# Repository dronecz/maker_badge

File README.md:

# Info
This project was moved [here](https://github.com/makerfaireczech/maker_badge)

## Where I can buy it? 

[Makermarket](https://www.makermarket.cz/maker-badge/)

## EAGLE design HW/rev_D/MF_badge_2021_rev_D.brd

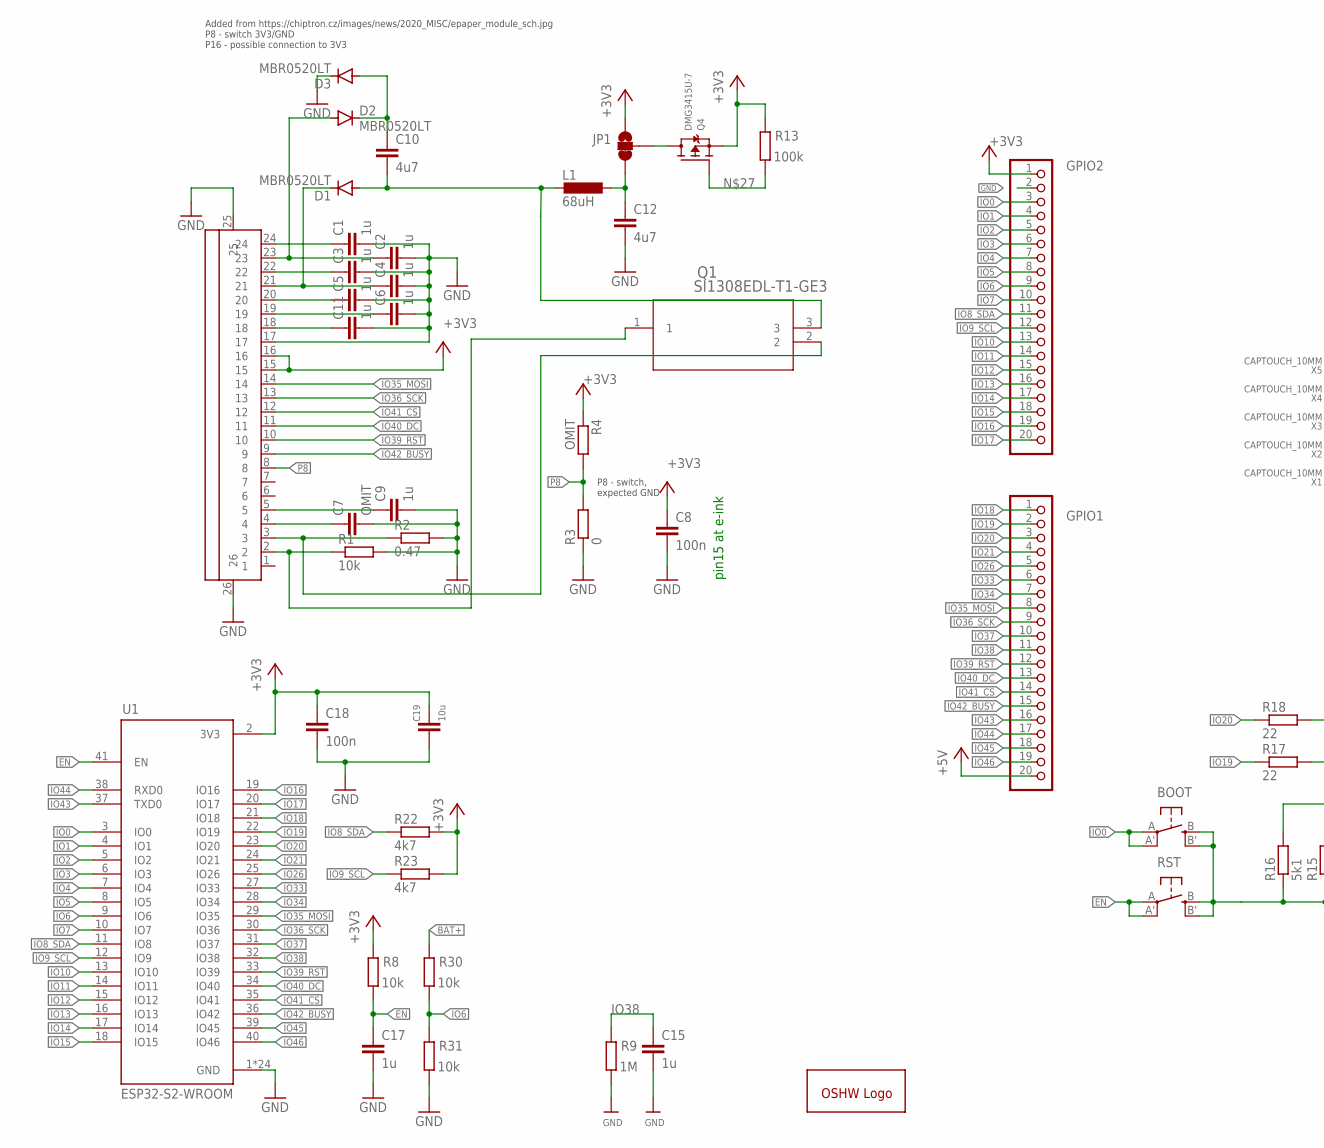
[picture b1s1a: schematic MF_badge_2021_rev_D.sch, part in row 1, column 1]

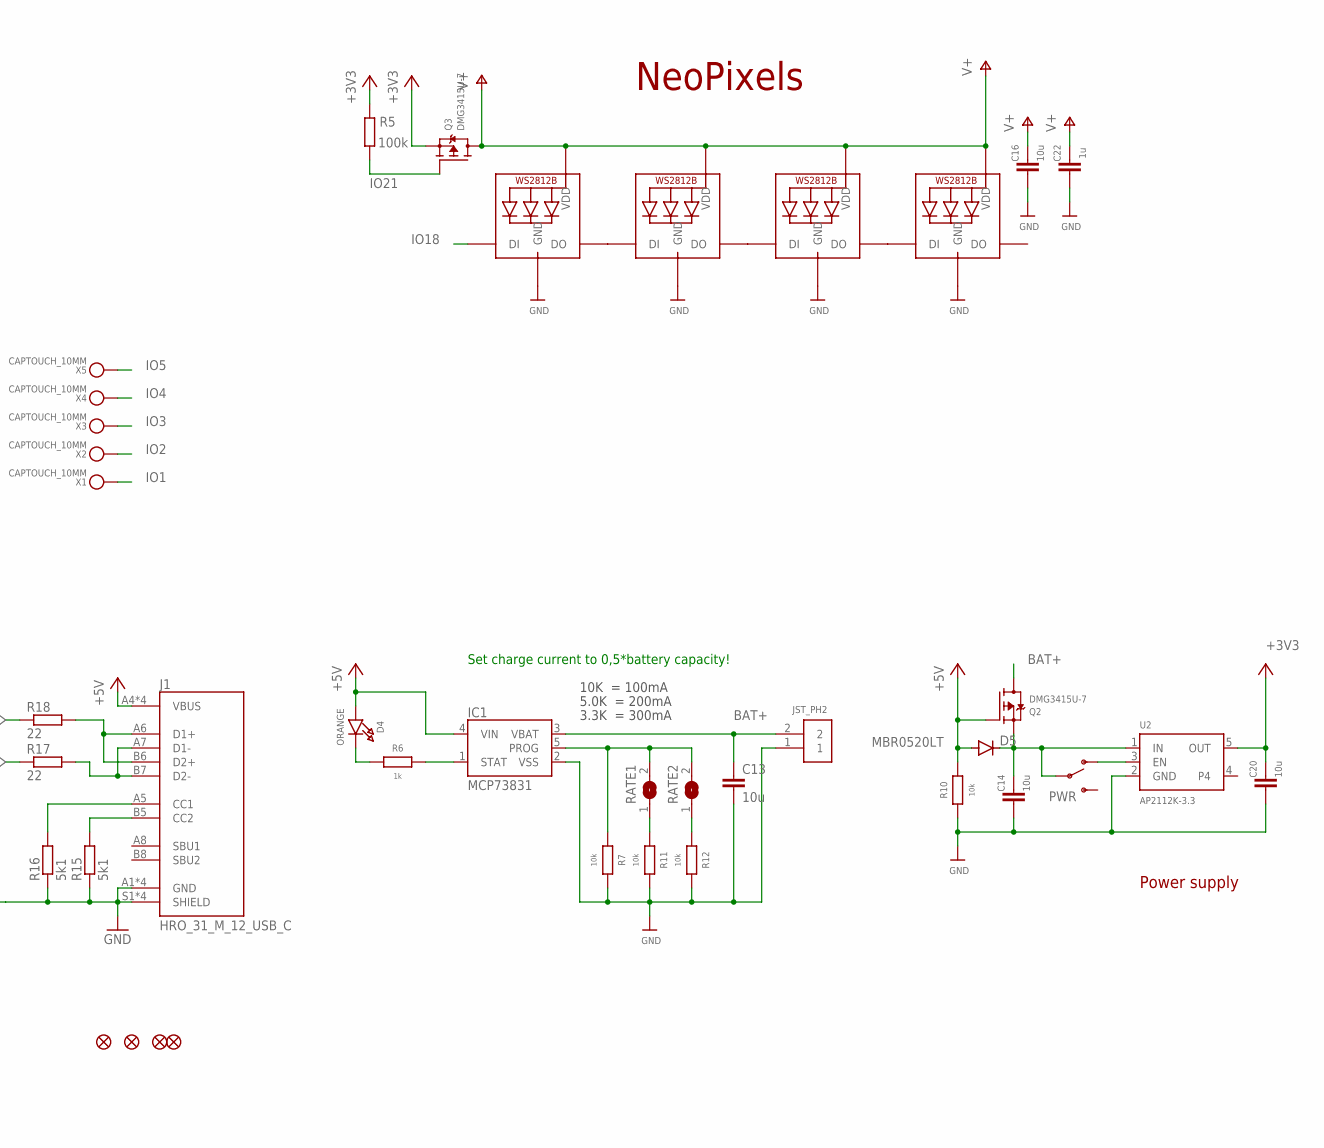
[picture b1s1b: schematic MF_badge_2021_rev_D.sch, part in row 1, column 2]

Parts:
BOOT: BUTTON_KMR2_4.6X2.8
C1, C2, C3, C4, C5, C6, C9, C11, C15, C17, C22: 1u; C0805
C7: OMIT; C0805
C8, C18: 100n; C0805
C10, C12: 4u7; C0805
C13, C14, C16, C19, C20: 10u; C0805
D1, D2, D3, D5: MBR0520LT; SOD123
D4: ORANGE; CHIPLED_0805_NOOUTLINE
FID1, FID2, FID3, FID4: FIDUCIAL_1MM
GOLD_ORB_SM1: OSHWLOGO_; OSHW_5MM_LOGO
GPIO1, GPIO2: PINHD-1X20; 1X20
IC1: MCP73831; SOT95P290X120-5
J1: HRO_31_M_12_USB_C
JP1: JUMPER-SMT_3_1-NC_TRACE_NO-SILK; SMT-JUMPER_3_1-NC_TRACE_NO-SILK
L1: 68uH; L4532P
LED2, LED3, LED4, LED5: WS2812B5050; WS2812B
PWR: SWITCH-SPDT-SMD-RIGHT-ANGLE; SWITCH_SPST_SMD_A
Q1: SI1308EDL-T1-GE3; MOSFET_8EDL-T1-GE3_VIS
Q2, Q3, Q4: DMG3415U-7; SOT23-R
R1, R7, R8, R10, R11, R12, R30, R31: 10k; R0805
R2: 0.47; R0805
R3: 0; R0805
R4: OMIT; R0805
R5, R13: 100k; R0805
R6: 1k; R0805
R9: 1M; R0805
R15, R16: 5k1; R0805
R17, R18: 22; R0805
R22, R23: 4k7; R0805
RATE1, RATE2: SOLDERJUMPER; SOLDERJUMPER_ARROW_NOPASTE
RST: BUTTON_KMR2_4.6X2.8
U1: ESP32-S2-WROOM; XCVR_ESP32-S2-WROOM
U2: AP2112K-3.3; SOT23-5
U$1: 2.13_EINK
U$8: JST_PH2; JSTPH2
X1, X2, X3, X4, X5: CAPTOUCH_10MM; CAPTOUCH_6X9MM

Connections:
+3V3: C8.1, C18.1, C19.1, C20.1, GPIO2.1, JP1.1, Q3.2 (S), Q4.2 (S), R4.1, R5.2, R8.2, R13.2, R22.2, R23.2, U1.2 (3V3), U2.5 (OUT), U$1.15, U$1.16
+5V: D4.A, D5.A, GPIO1.20, IC1.4 (VIN), J1.A4 (VBUS), J1.A9 (VBUS), J1.B4 (VBUS), J1.B9 (VBUS), Q2.1 (G), R10.2
BAT+: C13.1, IC1.3 (VBAT), Q2.3 (D), R30.2, U$8.2
D+_CON: J1.A6 (D1+), J1.B6 (D2+), R18.2
D-_CON: J1.A7 (D1-), J1.B7 (D2-), R17.2
EN: C17.1, R8.1, RST.A, RST.A' (P1), U1.41 (EN)
GND: BOOT.B (S), BOOT.B' (S1), C1.2, C2.2, C3.2, C4.2, C5.2, C6.2, C7.2, C8.2, C9.2, C11.2, C12.2, C13.2, C14.2, C15.2, C16.2, C17.2, C18.2, C19.2, C20.2, C22.2, D3.C, GPIO2.2, IC1.2 (VSS), J1.A1 (GND), J1.A12 (GND), J1.B1 (GND), J1.B12 (GND), J1.S1 (SHIELD), J1.S2 (SHIELD), J1.S3 (SHIELD), J1.S4 (SHIELD), LED2.3-GND (GND), LED3.3-GND (GND), LED4.3-GND (GND), LED5.3-GND (GND), R1.2, R2.2, R3.1, R7.2, R9.1, R10.1, R11.2, R12.2, R15.1, R16.1, R31.1, RST.B (S), RST.B' (S1), U1.1 (GND), U1.26 (GND), U1.42 (GND), U1.43.1 (GND), U1.43.2 (GND), U1.43.3 (GND), U1.43.4 (GND), U1.43.5 (GND), U1.43.6 (GND), U1.43.7 (GND), U1.43.8 (GND), U1.43.9 (GND), U1.43.10 (GND), U1.43.11 (GND), U1.43.12 (GND), U1.43.13 (GND), U1.43.14 (GND), U1.43.15 (GND), U1.43.16 (GND), U1.43.17 (GND), U1.43.18 (GND), U1.43.19 (GND), U1.43.20 (GND), U1.43.21 (GND), U2.2 (GND), U$1.17, U$1.25, U$1.26, U$8.1
IO0: BOOT.A, BOOT.A' (P1), GPIO2.3, U1.3 (IO0)
IO1: GPIO2.4, U1.4 (IO1), X1.P$1
IO2: GPIO2.5, U1.5 (IO2), X2.P$1
IO3: GPIO2.6, U1.6 (IO3), X3.P$1
IO4: GPIO2.7, U1.7 (IO4), X4.P$1
IO5: GPIO2.8, U1.8 (IO5), X5.P$1
IO6: GPIO2.9, R30.1, R31.2, U1.9 (IO6)
IO7: GPIO2.10, U1.10 (IO7)
IO8_SDA: GPIO2.11, R22.1, U1.11 (IO8)
IO9_SCL: GPIO2.12, R23.1, U1.12 (IO9)
IO10: GPIO2.13, U1.13 (IO10)
IO11: GPIO2.14, U1.14 (IO11)
IO12: GPIO2.15, U1.15 (IO12)
IO13: GPIO2.16, U1.16 (IO13)
IO14: GPIO2.17, U1.17 (IO14)
IO15: GPIO2.18, U1.18 (IO15)
IO16: GPIO2.19, U1.19 (IO16)
IO17: GPIO2.20, U1.20 (IO17)
IO18: GPIO1.1, LED2.4-DIN (DI), U1.21 (IO18)
IO19: GPIO1.2, R17.1, U1.22 (IO19)
IO20: GPIO1.3, R18.1, U1.23 (IO20)
IO21: GPIO1.4, Q3.1 (G), R5.1, U1.24 (IO21)
IO26: GPIO1.5, U1.25 (IO26)
IO33: GPIO1.6, U1.27 (IO33)
IO34: GPIO1.7, U1.28 (IO34)
IO35_MOSI: GPIO1.8, U1.29 (IO35), U$1.14
IO36_SCK: GPIO1.9, U1.30 (IO36), U$1.13
IO37: GPIO1.10, U1.31 (IO37)
IO38: C15.1, GPIO1.11, R9.2, U1.32 (IO38)
IO39_RST: GPIO1.12, U1.33 (IO39), U$1.10
IO40_DC: GPIO1.13, U1.34 (IO40), U$1.11
IO41_CS: GPIO1.14, U1.35 (IO41), U$1.12
IO42_BUSY: GPIO1.15, U1.36 (IO42), U$1.9
IO43: GPIO1.16, U1.37 (TXD0)
IO44: GPIO1.17, U1.38 (RXD0)
IO45: GPIO1.18, U1.39 (IO45)
IO46: GPIO1.19, U1.40 (IO46)
unnamed: C1.1, U$1.24
unnamed: C2.1, D2.A, U$1.23
unnamed: C3.1, U$1.22
unnamed: C4.1, D1.C, U$1.21
unnamed: C5.1, U$1.20
unnamed: C6.1, U$1.19
unnamed: C11.1, U$1.18
unnamed: IC1.1 (STAT), R6.2
unnamed: C14.1, D5.C, PWR.2, Q2.2 (S), U2.1 (IN)
unnamed: Q1.2, R2.1, U$1.3
unnamed: C9.1, U$1.5
unnamed: C7.1, U$1.4
unnamed: Q1.1, R1.1, U$1.2
unnamed: D4.C, R6.1
unnamed: C10.1, D2.C, D3.A
unnamed: LED2.2-DOUT (DO), LED3.4-DIN (DI)
unnamed: PWR.1 (O), U2.3 (EN)
unnamed: C10.2, D1.A, L1.2, Q1.3
unnamed: R11.1, RATE1.1
unnamed: R12.1, RATE2.1
unnamed: LED4.2-DOUT (DO), LED5.4-DIN (DI)
unnamed: J1.B5 (CC2), R15.2
unnamed: J1.A5 (CC1), R16.2
unnamed: LED3.2-DOUT (DO), LED4.4-DIN (DI)
unnamed: C12.1, JP1.3, L1.1
unnamed: Q4.1 (G), R13.1
unnamed: JP1.2, Q4.3 (D)
P8: R3.2, R4.2, U$1.8
PROG: IC1.5 (PROG), R7.1, RATE1.2, RATE2.2
V+: C16.1, C22.1, LED2.1-VDD (VDD), LED3.1-VDD (VDD), LED4.1-VDD (VDD), LED5.1-VDD (VDD), Q3.3 (D)

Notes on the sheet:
P8 - switch, expected GND
Added from https://chiptron.cz/images/news/2020_MISC/epaper_module_sch.jpg P8 - switch 3V3/GND P16 - possible connection to 3V3
10K = 100mA
5.0K = 200mA
3.3K = 300mA
Set charge current to 0,5*battery capacity!
Power supply
pin15 at e-ink
NeoPixels

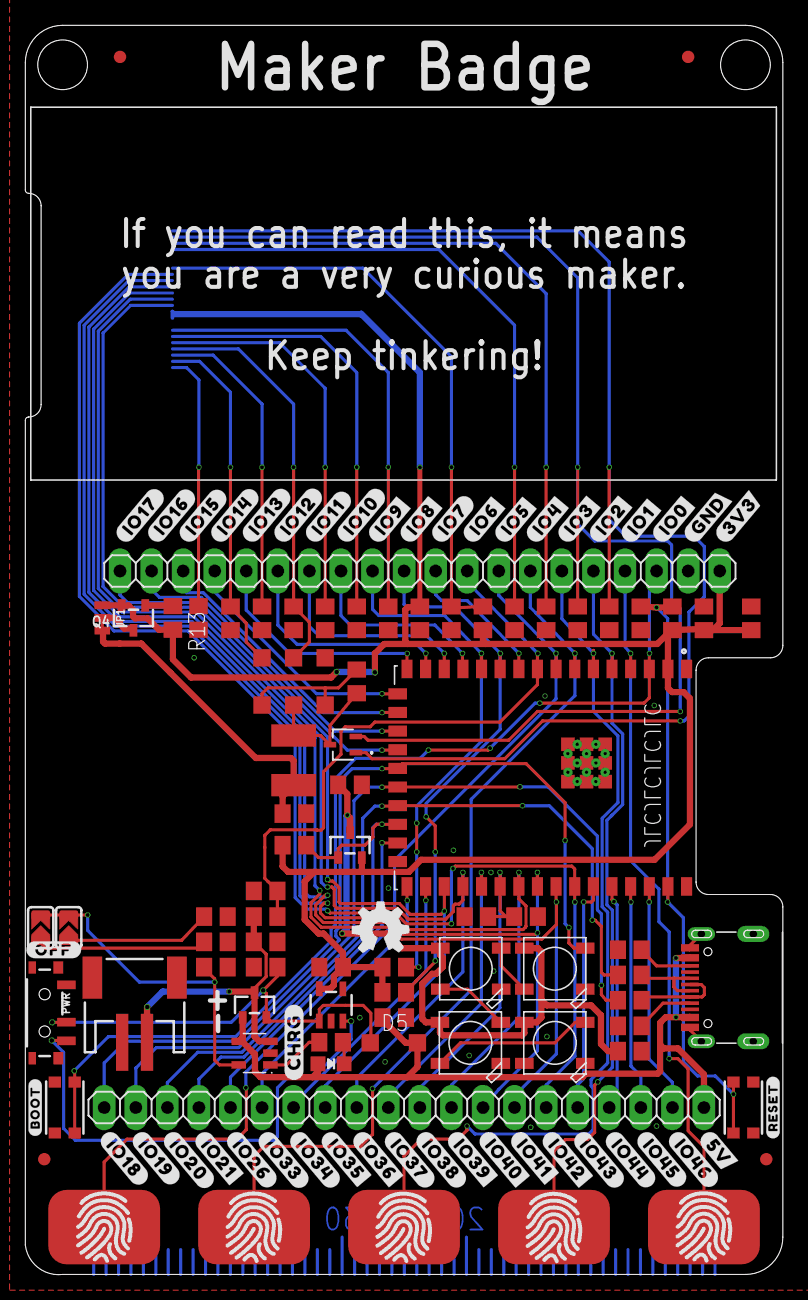
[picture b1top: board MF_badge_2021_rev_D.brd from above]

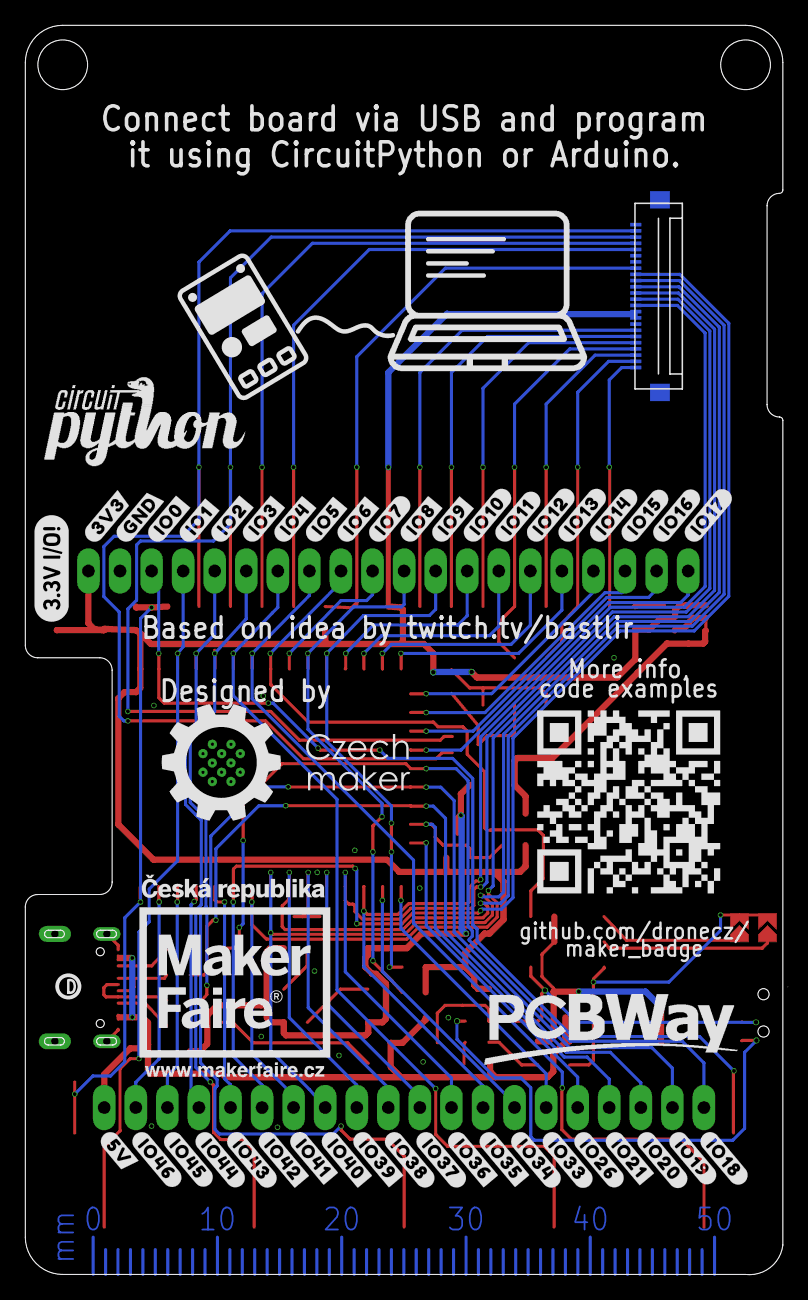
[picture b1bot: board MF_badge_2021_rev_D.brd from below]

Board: 2 copper layers, 61.0 x 100.5 mm, 165 parts (41 on the bottom side), 74 nets.

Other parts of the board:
U$2, U$92: #IO43#0
U$3, U$93: #IO44#0
U$4, U$33: #IO17#0
U$6, U$34: #IO16#0
U$7: #BOOT#0
U$9: #RESET#0
U$10: PCBFEAT-REV-040
U$12: #CHRG#0
U$16, U$77: #IO18#0
U$17, U$78: #IO19#0
U$18, U$79: #IO20#0
U$19, U$80: #IO21#0
U$20, U$81: #IO26#0
U$21, U$82: #IO33#0
U$22, U$83: #IO34#0
U$23, U$84: #IO35#0
U$24, U$85: #IO36#0
U$25, U$87: #IO38#0
U$26, U$86: #IO37#0
U$27, U$88: #IO39#0
U$28, U$89: #IO40#0
U$29, U$90: #IO41#0
U$30, U$91: #IO42#0
U$31, U$94: #IO45#0
U$32, U$95: #IO46#0
U$35, U$57: #IO15#0
U$37, U$58: #IO14#0
U$38, U$59: #IO13#0
U$39, U$60: #IO12#0
U$40, U$65: #IO11#0
U$41, U$66: #IO10#0
U$42, U$67: #IO9#0
U$43, U$68: #IO8#0
U$44, U$69: #IO7#0
U$45, U$70: #IO6#0
U$46, U$71: #IO5#0
U$47, U$72: #IO4#0
U$48, U$73: #IO3#0
U$49, U$74: #IO2#0
U$50, U$75: #IO1#0
U$51, U$76: #IO0#0
U$56: #OFF#0
U$96, U$100: #GND#0
U$97, U$101: #3V3#0
U$98, U$99: #5V#0

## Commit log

2021-11-21 Initial commit of files
2022-08-18 Update to latest HW version
2022-11-20 Update
    - changed filename for Arduino example code
    - add combined.bin for CPY
    - add example code from MF for CPY
2022-12-04 Added basic text example for Arduino
2022-12-04 Example folder name change
2022-12-24 Adding full test examplr for rev.B/C
2023-02-20 Add rev.C files
2023-02-20 Add rev_D -> work in progress
2023-03-09 Add rev.A example for CPY
2023-06-11 Closing repository
2023-06-11 Maker market address change

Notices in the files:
parts and their libraries:
microbuilder: This work is placed in the public domain, and may be freely used for commercial and non-commercial work with the following conditions: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
SparkFun-Jumpers: Licensing: Creative Commons ShareAlike 4.0 International - https://creativecommons.org/licenses/by-sa/4.0
